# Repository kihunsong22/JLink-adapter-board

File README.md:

# JLink-adapter-board
JLink adapter board with most used connectors

### List of Connectors
* 2.54mm 2*10 pin female socket connector (for connecting to J-Link)
* 2.54mm 2*10 pin IDC male header connector
* 2.54mm 2*5 pin IDC male header connector
* 2.00mm 2*5 pin IDC male header connector
* 1.27mm 2*5 pin IDC male header connector (supports both SMD and PTH)
* 2.54mm 2*3 pin IDC male header connector - for Tag-Connect cable: [TC2030-IDC-NL](https://www.tag-connect.com/product/tc2030-idc-nl)
* 2.54mm 4 pin XH2.54 connector
* 2.54mm 6 pin XH2.54 connector

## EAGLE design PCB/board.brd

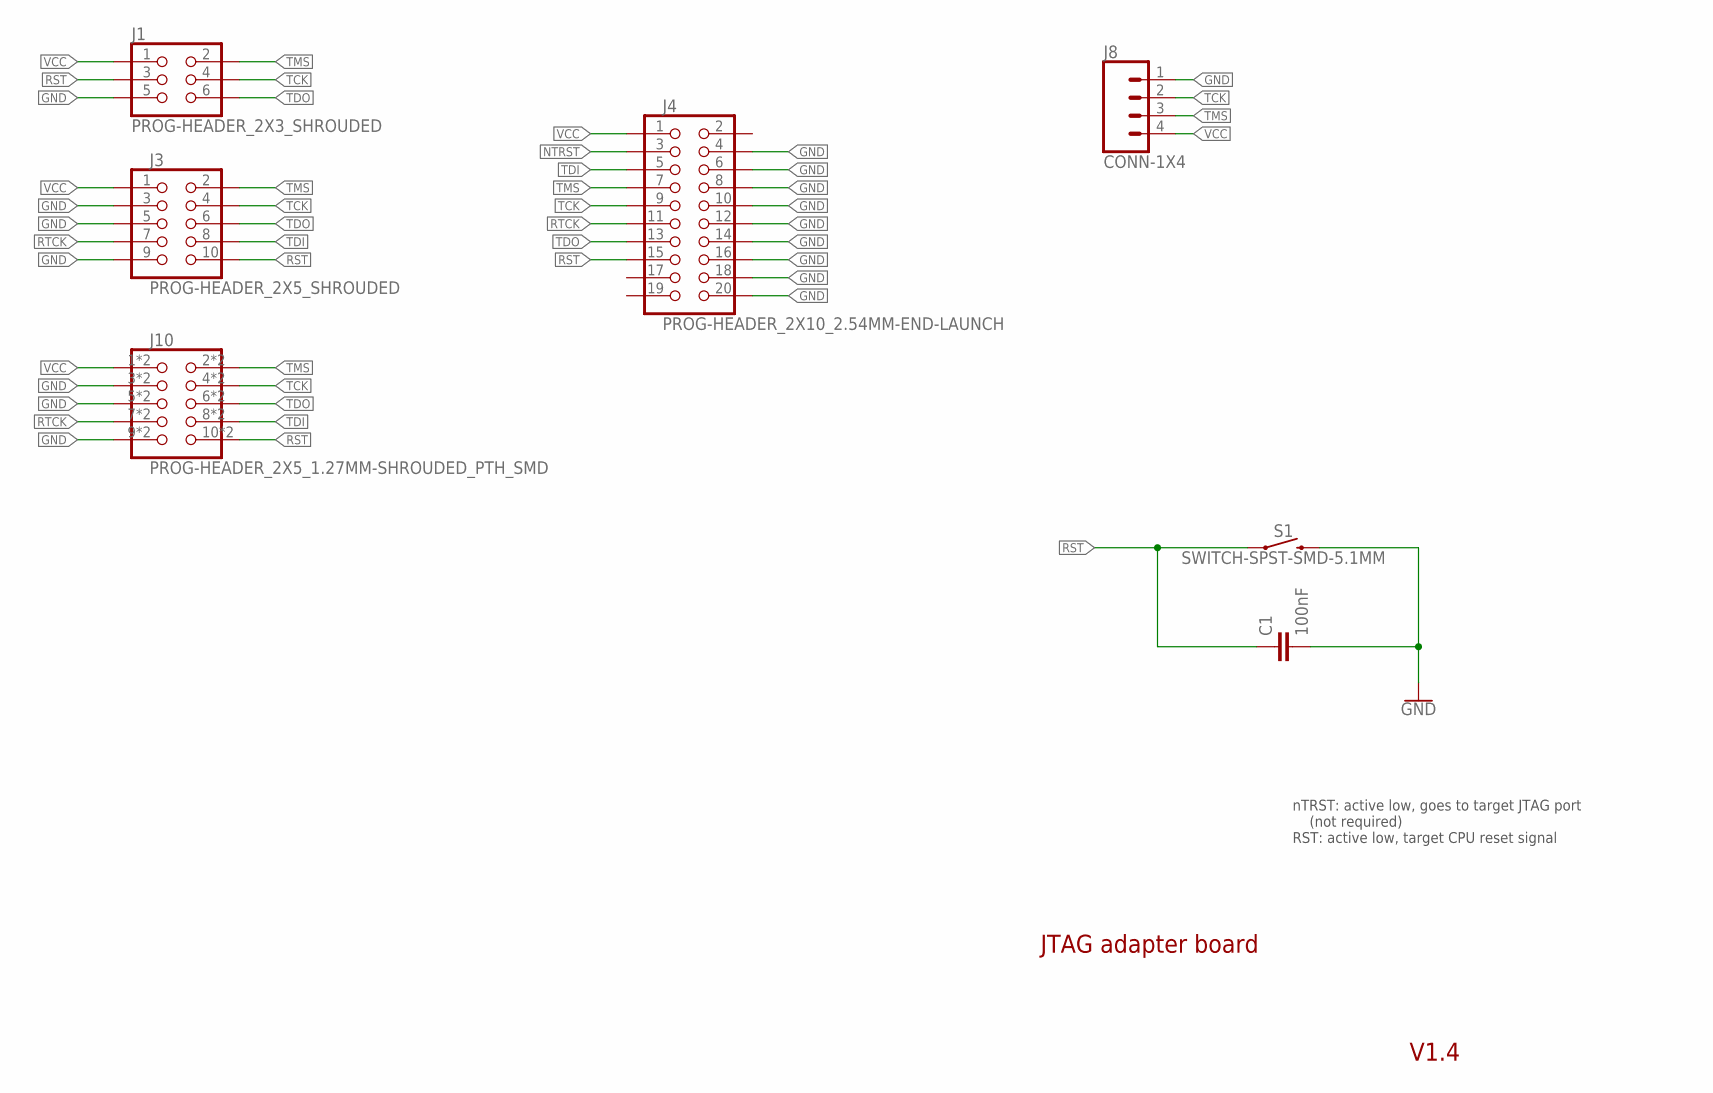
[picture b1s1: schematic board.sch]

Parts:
C1: 100nF; C0603
J1: PROG-HEADER_2X3_SHROUDED; 2X3-2.54MM-SHROUDED
J3: PROG-HEADER_2X5_SHROUDED; 2X5-2.54MM-SHROUDED
J4: PROG-HEADER_2X10_2.54MM-END-LAUNCH; 2X10-2.54MM-END-LAUNCH
J8: CONN-1X4; XH-4P-2.54MM
J10: PROG-HEADER_2X5_1.27MM-SHROUDED_PTH_SMD; 2X5-1.27MM-SHROUDED_PTH+SMD
S1: SWITCH-SPST-SMD-5.1MM; TACTILE_SWITCH_SMD_5.1MM

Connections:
2: J4.2
GND: C1.2, J1.5, J3.3, J3.5, J3.9, J4.4, J4.6, J4.8, J4.10, J4.12, J4.14, J4.16, J4.18, J4.20, J8.1, J10.3, J10.5, J10.9, J10.13 (3), J10.15 (5), J10.19 (9), S1.3 (2)
NTRST: J4.3
RST: C1.1, J1.3, J3.10, J4.15, J10.10, J10.20 (10), S1.1
RTCK: J3.7, J4.11, J10.7, J10.17 (7)
TCK: J1.4, J3.4, J4.9, J8.2, J10.4, J10.14 (4)
TDI: J3.8, J4.5, J10.8, J10.18 (8)
TDO: J1.6, J3.6, J4.13, J10.6, J10.16 (6)
TMS: J1.2, J3.2, J4.7, J8.3, J10.2, J10.12 (2)
VCC: J1.1, J3.1, J4.1, J8.4, J10.1, J10.11 (1)

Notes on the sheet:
nTRST: active low, goes to target JTAG port (not required) RST: active low, target CPU reset signal

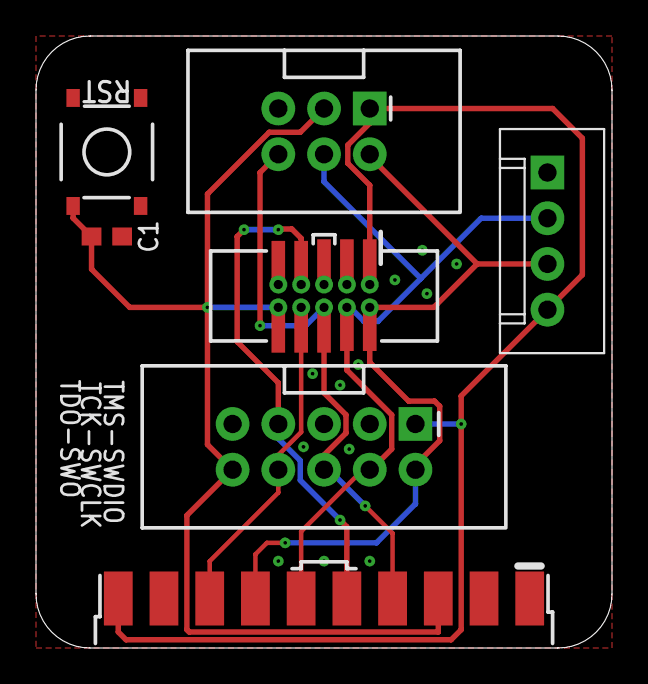
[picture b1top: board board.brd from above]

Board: 2 copper layers, 32.0 x 34.0 mm, 7 parts (0 on the bottom side), 8 nets.

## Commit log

2020-04-06 moved repo
2020-04-07 V1.1
2020-04-13 V1.2
2020-04-13 added pics, updated README
2020-04-13 compressed pics
2020-04-13 fixed weird text angle
2020-04-22 changed font size
2020-04-22 updated README for V1.2
2020-04-22 V1.3 - changed text orientation
2020-05-01 connected pin 5, 9 to GND
2020-05-15 changed right angle connector to end launch
2020-05-27 fixed footprint error
2020-08-01 V1.5
    - changed RST to TDI for 3*2 pin connector
    - optimized routing
2021-02-03 rollback to V1.4
2021-07-04 V1.6 update
2024-12-26 DNP'd capacitors to not reset target board, fixed connector part links
2025-07-16 removed temporary files and backups
2025-07-16 update .gitignore with KiCAD options

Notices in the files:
parts and their libraries:
SparkFun-Aesthetics: Licensing: Creative Commons ShareAlike 4.0 International - https://creativecommons.org/licenses/by-sa/4.0
